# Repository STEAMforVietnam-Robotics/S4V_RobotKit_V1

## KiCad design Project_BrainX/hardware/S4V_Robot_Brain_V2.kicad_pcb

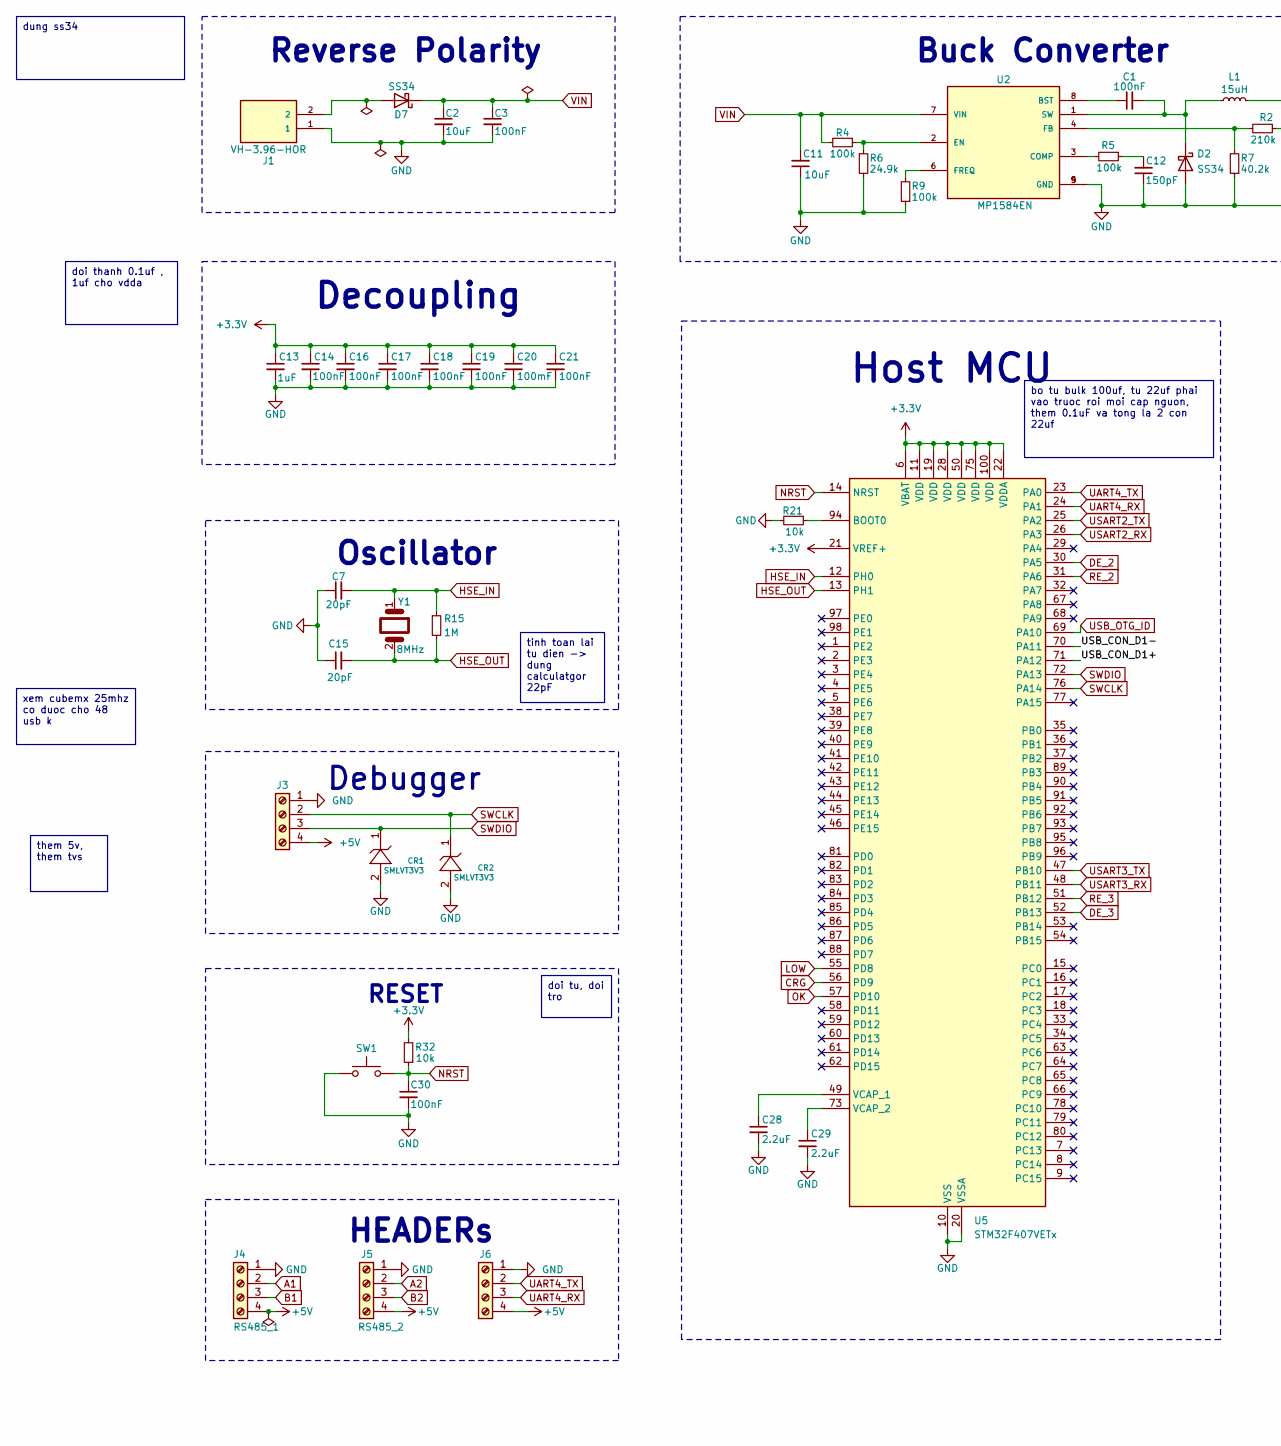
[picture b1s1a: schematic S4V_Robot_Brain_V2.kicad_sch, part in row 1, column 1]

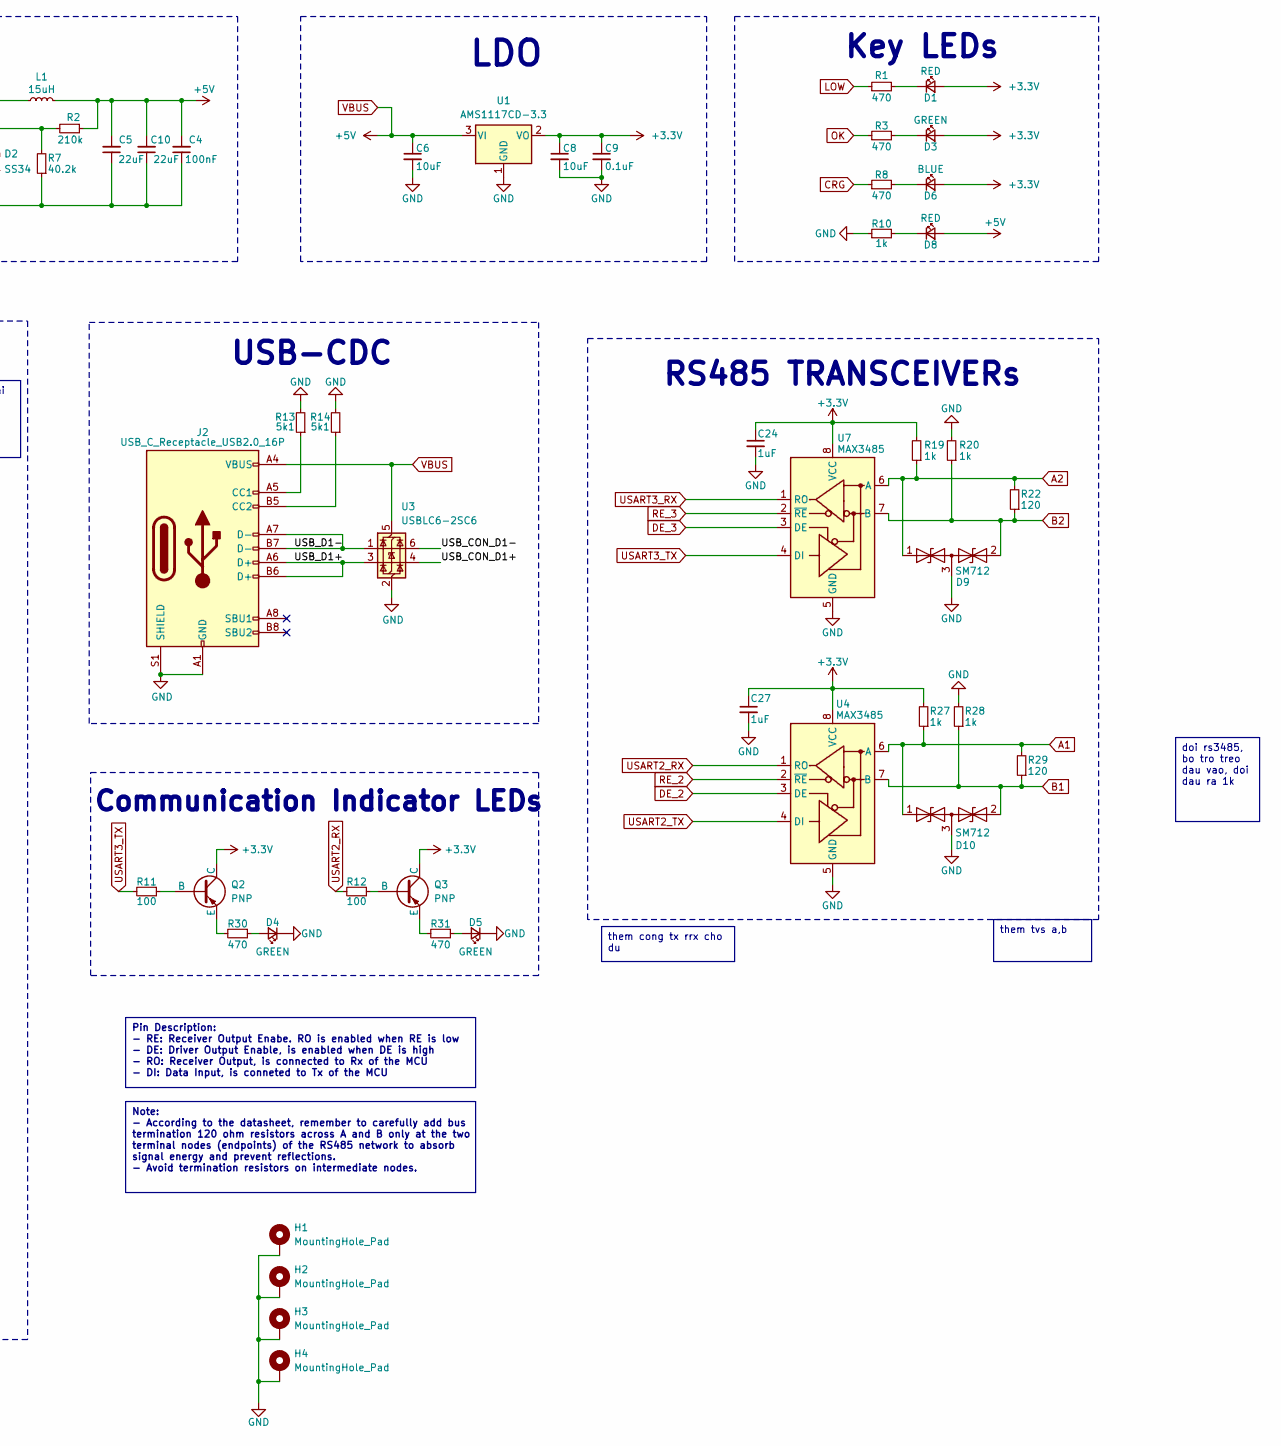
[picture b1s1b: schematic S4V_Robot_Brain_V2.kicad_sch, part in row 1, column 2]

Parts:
C1, C4, C14, C16, C17, C18, C19, C21, C30: 100nF; C_0603_1608Metric
C2: 10uF; C_0805_2012Metric
C3: 100nF; C_0805_2012Metric
C5, C10: 22uF; C_0603_1608Metric
C6, C8, C11: 10uF; C_0603_1608Metric
C7, C15: 20pF; C_0603_1608Metric
C9: 0.1uF; C_0603_1608Metric
C12: 150pF; C_0603_1608Metric
C13, C24, C27: 1uF; C_0603_1608Metric
C20: 100mF; C_0603_1608Metric
C28, C29: 2.2uF; C_0603_1608Metric
CR1, CR2: SMLVT3V3
D1, D8: RED; LED_0603_1608Metric
D2, D7: SS34; SS34_SMA
D3, D4, D5: GREEN; LED_0603_1608Metric
D6: BLUE; LED_0603_1608Metric
D9, D10: SM712; SOT-23
H1, H2, H3, H4: MountingHole_Pad; MountingHole_3.2mm_M3_Pad_Via
J1: VH-3.96-HOR; AMASS_XT60IPW-M_1x03_P7.20mm_Horizontal; PARTREV R
J2: USB_C_Receptacle_USB2.0_16P; USB_C_Receptacle_GCT_USB4105-xx-A_16P_TopMnt_Horizontal
J3: Screw_Terminal_01x04; PinHeader_1x04_P2.54mm_Vertical
J4: RS485_1; JST_SH_SM04B-SRSS-TB_1x04-1MP_P1.00mm_Horizontal
J5: RS485_2; JST_SH_SM04B-SRSS-TB_1x04-1MP_P1.00mm_Horizontal
J6: Screw_Terminal_01x04; JST_SH_SM04B-SRSS-TB_1x04-1MP_P1.00mm_Horizontal
L1: 15uH; L_7.3x7.3_H4.5
Q2, Q3: PNP; SOT-23
R1, R3, R8, R30, R31: 470; R_0603_1608Metric
R2: 210k; R_0603_1608Metric
R4, R5, R9: 100k; R_0603_1608Metric
R6: 24.9k; R_0603_1608Metric
R7: 40.2k; R_0603_1608Metric
R10, R19, R20, R27, R28: 1k; R_0603_1608Metric
R11, R12: 100; R_0603_1608Metric
R13, R14: 5k1; R_0603_1608Metric
R15: 1M; R_0603_1608Metric
R21, R32: 10k; R_0603_1608Metric
R22, R29: 120; R_0603_1608Metric
SW1: SW_Push_1TS009xxxx-xxxx-xxxx_6x6x5mm
U1: AMS1117CD-3.3; SOT-223-3_TabPin2
U2: MP1584EN
U3: USBLC6-2SC6; SOT-23-6
U4, U7: MAX3485; SOIC-8_3.9x4.9mm_P1.27mm
U5: STM32F407VETx; LQFP-100_14x14mm_P0.5mm
Y1: 8MHz; Crystal_SMD_5032-2Pin_5.0x3.2mm

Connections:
+3.3V: C8.1, C9.1, C13.1, C14.1, C16.1, C17.1, C18.1, C19.1, C20.1, C21.1, C24.1, C27.1, D1.2 (A), D3.2 (A), D6.2 (A), Q2.1 (C), Q3.1 (C), R19.2, R27.2, R32.2, U1.2 (VO), U4.8 (VCC), U5.6 (VBAT), U5.11 (VDD), U5.19 (VDD), U5.21 (VREF+), U5.22 (VDDA), U5.28 (VDD), U5.50 (VDD), U5.75 (VDD), U5.100 (VDD), U7.8 (VCC)
/USB_CON_D1+: U3.4 (I/O2), U5.71 (PA12)
/USB_CON_D1-: U3.6 (I/O1), U5.70 (PA11)
/USB_D1+: J2.A6 (D+), J2.B6 (D+), U3.3 (I/O2)
/USB_D1-: J2.A7 (D-), J2.B7 (D-), U3.1 (I/O1)
A1: D10.1 (A1), J4.2, R27.1, R29.2, U4.6 (A)
A2: D9.1 (A1), J5.2, R19.1, R22.2, U7.6 (A)
B1: D10.2 (A2), J4.3, R28.1, R29.1, U4.7 (B)
B2: D9.2 (A2), J5.3, R20.1, R22.1, U7.7 (B)
CRG: R8.1, U5.56 (PD9)
DE_2: U4.3 (DE), U5.30 (PA5)
DE_3: U5.52 (PB13), U7.3 (DE)
GND: C2.2, C3.2, C4.1, C5.1, C6.2, C7.1, C8.2, C9.2, C10.1, C11.1, C12.1, C13.2, C14.2, C15.1, C16.2, C17.2, C18.2, C19.2, C20.2, C21.2, C24.2, C27.2, C28.2, C29.2, C30.2, CR1.2, CR2.2, D2.2 (A), D4.1 (K), D5.1 (K), D9.3 (common), D10.3 (common), H1.1, H2.1, H3.1, H4.1, J1.1, J2.A1 (GND), J2.A12 (GND), J2.B1 (GND), J2.B12 (GND), J2.S1 (SHIELD), J3.1, J4.1, J5.1, J6.1, R6.2, R7.1, R9.1, R10.1, R13.2, R14.2, R20.2, R21.2, R28.2, SW1.1, U1.1 (GND), U2.5 (GND), U2.9 (GND), U3.2 (GND), U4.5 (GND), U5.10 (VSS), U5.20 (VSSA), U5.27 (VSS), U5.74 (VSS), U5.99 (VSS), U7.5 (GND)
HSE_IN: C7.2, R15.1, U5.12 (PH0), Y1.1
HSE_OUT: C15.2, R15.2, U5.13 (PH1), Y1.2
LOW: R1.1, U5.55 (PD8)
NRST: C30.1, R32.1, SW1.2, U5.14 (NRST)
unnamed: C12.2, R5.1
unnamed: D1.1 (K), R1.2
unnamed: C1.2, D2.1 (K), L1.1, U2.1 (SW)
unnamed: D3.1 (K), R3.2
unnamed: D4.2 (A), R30.1
unnamed: D5.2 (A), R31.1
unnamed: D6.1 (K), R8.2
unnamed: D7.2 (A), J1.2
unnamed: D8.1 (K), R10.2
unnamed: J2.A5 (CC1), R13.1
unnamed: J2.B5 (CC2), R14.1
unnamed: Q2.2 (B), R11.1
unnamed: Q2.3 (E), R30.2
unnamed: Q3.2 (B), R12.1
unnamed: Q3.3 (E), R31.2
unnamed: C1.1, U2.8 (BST)
unnamed: R5.2, U2.3 (COMP)
unnamed: R4.1, R6.1, U2.2 (EN)
unnamed: R2.2, R7.2, U2.4 (FB)
unnamed: R9.2, U2.6 (FREQ)
unnamed: R21.1, U5.94 (BOOT0)
unnamed: C28.1, U5.49 (VCAP_1)
unnamed: C29.1, U5.73 (VCAP_2)
OK: R3.1, U5.57 (PD10)
RE_2: U4.2 (~RE), U5.31 (PA6)
RE_3: U5.51 (PB12), U7.2 (~RE)
SWCLK: CR2.1, J3.2, U5.76 (PA14)
SWDIO: CR1.1, J3.3, U5.72 (PA13)
UART4_RX: J6.3, U5.24 (PA1)
UART4_TX: J6.2, U5.23 (PA0)
USART2_RX: R12.2, U4.1 (RO), U5.26 (PA3)
USART2_TX: U4.4 (DI), U5.25 (PA2)
USART3_RX: U5.48 (PB11), U7.1 (RO)
USART3_TX: R11.2, U5.47 (PB10), U7.4 (DI)
USB_OTG_ID: U5.69 (PA10)
VBUS: C4.2, C5.2, C6.1, C10.2, D8.2 (A), J2.A4 (VBUS), J2.A9 (VBUS), J2.B4 (VBUS), J2.B9 (VBUS), J3.4, J4.4, J5.4, J6.4, L1.2, R2.1, U1.3 (VI), U3.5 (VBUS)
VIN: C2.1, C3.1, C11.2, D7.1 (K), R4.2, U2.7 (VIN)

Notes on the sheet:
them 5v, them tvs
Pin Description: - RE: Receiver Output Enabe. RO is enabled when RE is low - DE: Driver Output Enable, is enabled when DE is high - RO: Receiver Output, is connected to Rx of the MCU - DI: Data Input, is conneted to Tx of the MCU
doi rs3485, bo tro treo dau vao, doi dau ra 1k
xem cubemx 25mhz co duoc cho 48 usb k
them tvs a,b
them cong tx rrx cho du
doi thanh 0.1uf , 1uf cho vdda
tinh toan lai tu dien -> dung calculatgor 22pF
bo tu bulk 100uf, tu 22uf phai vao truoc roi moi cap nguon, them 0.1uF va tong la 2 con 22uf
doi tu, doi tro
dung ss34
Note: - According to the datasheet, remember to carefully add bus termination 120 ohm resistors across A and B only at the two terminal nodes (endpoints) of the RS485 network to absorb signal energy and prevent reflections. - Avoid termination resistors on intermediate nodes.
Decoupling
Key LEDs
USB-CDC
RS485 TRANSCEIVERs
LDO
Oscillator
Communication Indicator LEDs
Debugger
Buck Converter
RESET
Host MCU
Reverse Polarity
HEADERs

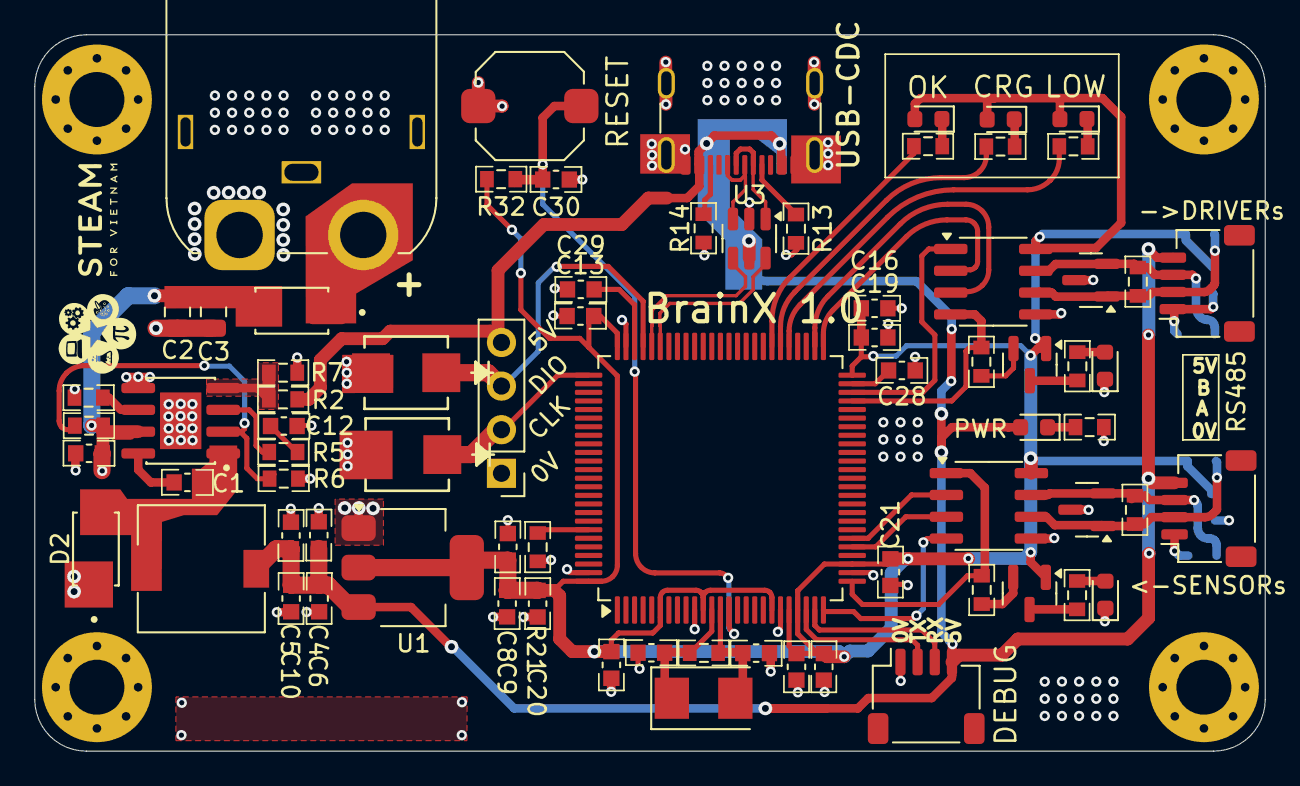
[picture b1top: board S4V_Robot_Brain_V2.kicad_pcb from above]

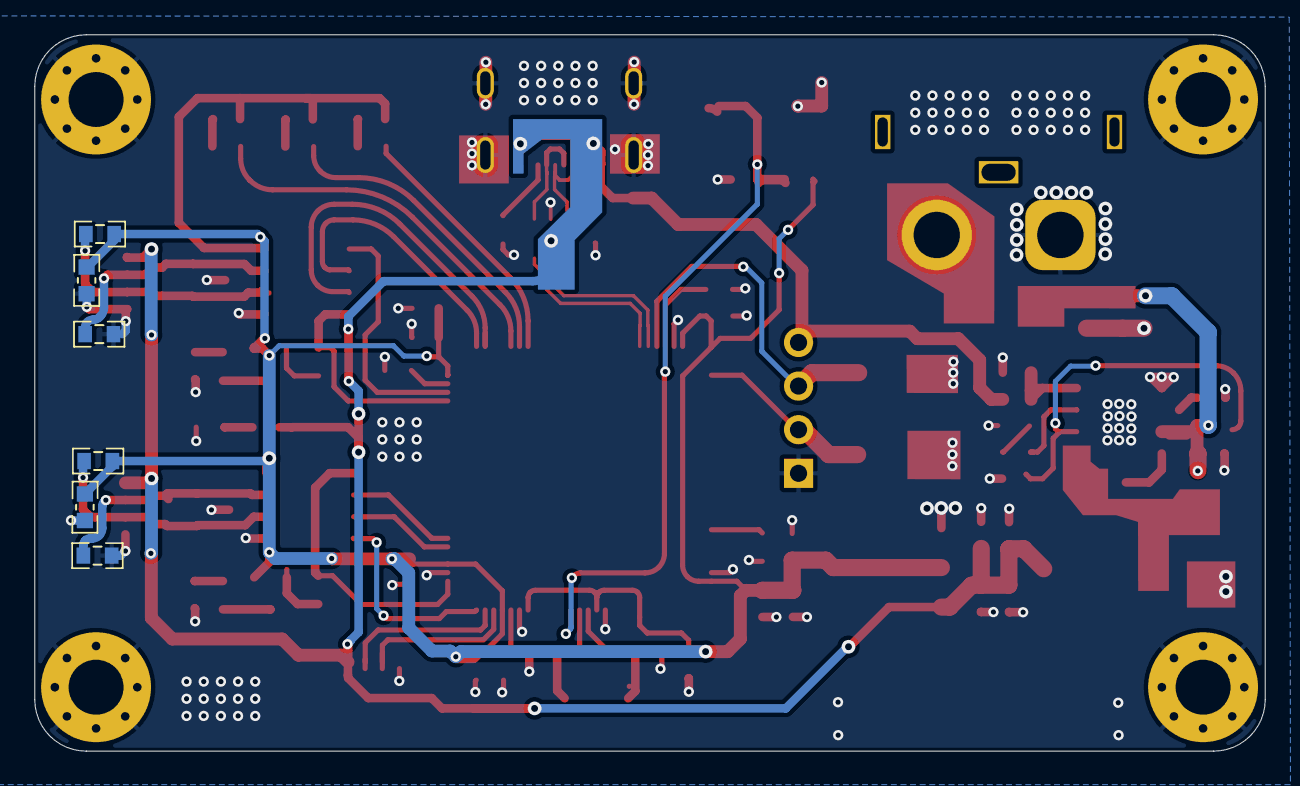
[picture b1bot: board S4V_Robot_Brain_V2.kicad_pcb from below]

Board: 2 copper layers, 71.7 x 41.7 mm, 84 parts (6 on the bottom side), 53 nets.

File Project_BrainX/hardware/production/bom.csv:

Designator,Footprint,Quantity,Value,LCSC Part #
"C1, C14, C16, C17, C18, C19, C21, C30, C4",0603,9,100nF,
"C10, C5",0603,2,22uF,
"C11, C6, C8",0603,3,10uF,
C12,0603,1,150pF,
"C13, C24, C27",0603,3,1uF,
"C15, C7",0603,2,20pF,
C2,0805,1,10uF,
C20,0603,1,100mF,
"C28, C29",0603,2,2.2uF,
C3,0805,1,100nF,
C9,0603,1,0.1uF,
"CR1, CR2",SMLVT3V3,2,SMLVT3V3,
"D1, D8",0603,2,RED,
"D10, D9",SOT-23,2,SM712,
"D2, D7",SS34_SMA,2,SS34,
"D3, D4, D5",0603,3,GREEN,
D6,0603,1,BLUE,
J1,AMASS_XT60IPW-M_1x03_P7.20mm_Horizontal,1,VH-3.96-HOR,
J2,USB_C_Receptacle_GCT_USB4105-xx-A_16P_TopMnt_Horizontal,1,USB_C_Receptacle_USB2.0_16P,
J3,PinHeader_1x04_P2.54mm_Vertical,1,Screw_Terminal_01x04,
J4,JST_SH_SM04B-SRSS-TB_1x04-1MP_P1.00mm_Horizontal,1,RS485_1,
J5,JST_SH_SM04B-SRSS-TB_1x04-1MP_P1.00mm_Horizontal,1,RS485_2,
J6,JST_SH_SM04B-SRSS-TB_1x04-1MP_P1.00mm_Horizontal,1,Screw_Terminal_01x04,
L1,L_7.3x7.3_H4.5,1,15uH,
"Q2, Q3",SOT-23,2,PNP,
"R1, R3, R30, R31, R8",0603,5,470,
"R10, R19, R20, R27, R28",0603,5,1k,
"R11, R12",0603,2,100,
"R13, R14",0603,2,5k1,
R15,0603,1,1M,
R2,0603,1,210k,
"R21, R32",0603,2,10k,
"R22, R29",0603,2,120,
"R4, R5, R9",0603,3,100k,
R6,0603,1,24.9k,
R7,0603,1,40.2k,
SW1,SW_Push_1TS009xxxx-xxxx-xxxx_6x6x5mm,1,~,
U1,SOT-223-3_TabPin2,1,AMS1117CD-3.3,
U2,MP1584EN,1,MP1584EN,
U3,SOT-23-6,1,USBLC6-2SC6,
"U4, U7",SOIC-8_3.9x4.9mm_P1.27mm,2,MAX3485,
U5,LQFP-100_14x14mm_P0.5mm,1,STM32F407VETx,
Y1,Crystal_SMD_5032-2Pin_5.0x3.2mm,1,8MHz,

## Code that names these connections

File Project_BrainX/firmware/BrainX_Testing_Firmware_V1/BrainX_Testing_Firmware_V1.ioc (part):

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Mcu.Name=STM32F407V(E-G)Tx
Mcu.Package=LQFP100
Mcu.UserName=STM32F407VETx
PA0-WKUP.Mode=Asynchronous
PA0-WKUP.Signal=UART4_TX
PA1.Mode=Asynchronous
PA1.Signal=UART4_RX
PA11.Mode=Device_Only
PA11.Signal=USB_OTG_FS_DM
PA12.Mode=Device_Only
PA12.Signal=USB_OTG_FS_DP
PA13.Mode=Serial_Wire
PA13.Signal=SYS_JTMS-SWDIO
PA14.Mode=Serial_Wire
PA14.Signal=SYS_JTCK-SWCLK
PA2.Mode=Asynchronous
PA2.Signal=USART2_TX
PA3.Mode=Asynchronous
PA3.Signal=USART2_RX
PA5.GPIOParameters=GPIO_Label
PA5.GPIO_Label=DE_2
PA5.Signal=GPIO_Output
PA6.GPIOParameters=PinState,GPIO_Label
PA6.GPIO_Label=RE_2
PA6.PinState=GPIO_PIN_SET
PA6.Signal=GPIO_Output
PB10.Mode=Asynchronous
PB10.Signal=USART3_TX
PB11.Mode=Asynchronous
PB11.Signal=USART3_RX
PD10.GPIOParameters=PinState,GPIO_Label
PD10.GPIO_Label=OK
PD10.PinState=GPIO_PIN_SET
PD10.Signal=GPIO_Output
PD8.GPIOParameters=GPIO_Speed,PinState,GPIO_PuPd,GPIO_Label,GPIO_ModeDefaultOutputPP
PD8.GPIO_Label=LOW
PD8.GPIO_ModeDefaultOutputPP=GPIO_MODE_OUTPUT_OD
PD8.GPIO_PuPd=GPIO_NOPULL
PD8.GPIO_Speed=GPIO_SPEED_FREQ_LOW
PD8.PinState=GPIO_PIN_SET
PD8.Signal=GPIO_Output
PD9.GPIOParameters=PinState,GPIO_PuPd,GPIO_Label,GPIO_ModeDefaultOutputPP
PD9.GPIO_Label=CRG
PD9.GPIO_ModeDefaultOutputPP=GPIO_MODE_OUTPUT_OD
PD9.GPIO_PuPd=GPIO_NOPULL
PD9.PinState=GPIO_PIN_SET
PD9.Signal=GPIO_Output
PH0-OSC_IN.Mode=HSE-External-Oscillator
PH0-OSC_IN.Signal=RCC_OSC_IN
PH1-OSC_OUT.Mode=HSE-External-Oscillator
PH1-OSC_OUT.Signal=RCC_OSC_OUT
RCC.HSE_VALUE=8000000
RCC.SYSCLKFreq_VALUE=168000000
RCC.SYSCLKSource=RCC_SYSCLKSOURCE_PLLCLK
board=custom

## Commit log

2026-01-08 First commit: BrainX_Testing_Firmware_V1: RS485_Driver
2026-01-11 firmware/rs485-driver: add tx api-s
2026-01-11 add hardware/ directory
2026-02-11 write brainx_usbcdc driver and brainx_sys
2026-02-12 update brainX firmware system_flowchart + refactor usbcdc variables name + add interrupt for LED display
2026-02-26 project_motor_driver/firmware: add flash eeprom emulation files
2026-02-26 project_motor_driver_board/firmware: add hardware client flowchart
2026-02-28 Project_Motor_Driver_Board/firmware: done flash eeprom emulatorto store unique board id for stm32f1xx devices
2026-02-28 Project_Motor_Driver_Board/firmware: add timer, rs485 driver and mtdriver_sys files
